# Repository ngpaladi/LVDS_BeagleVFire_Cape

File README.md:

# LVDS_BeagleVFire_Cape
Cape for LVDS inputs to a BeagleV Fire TDC

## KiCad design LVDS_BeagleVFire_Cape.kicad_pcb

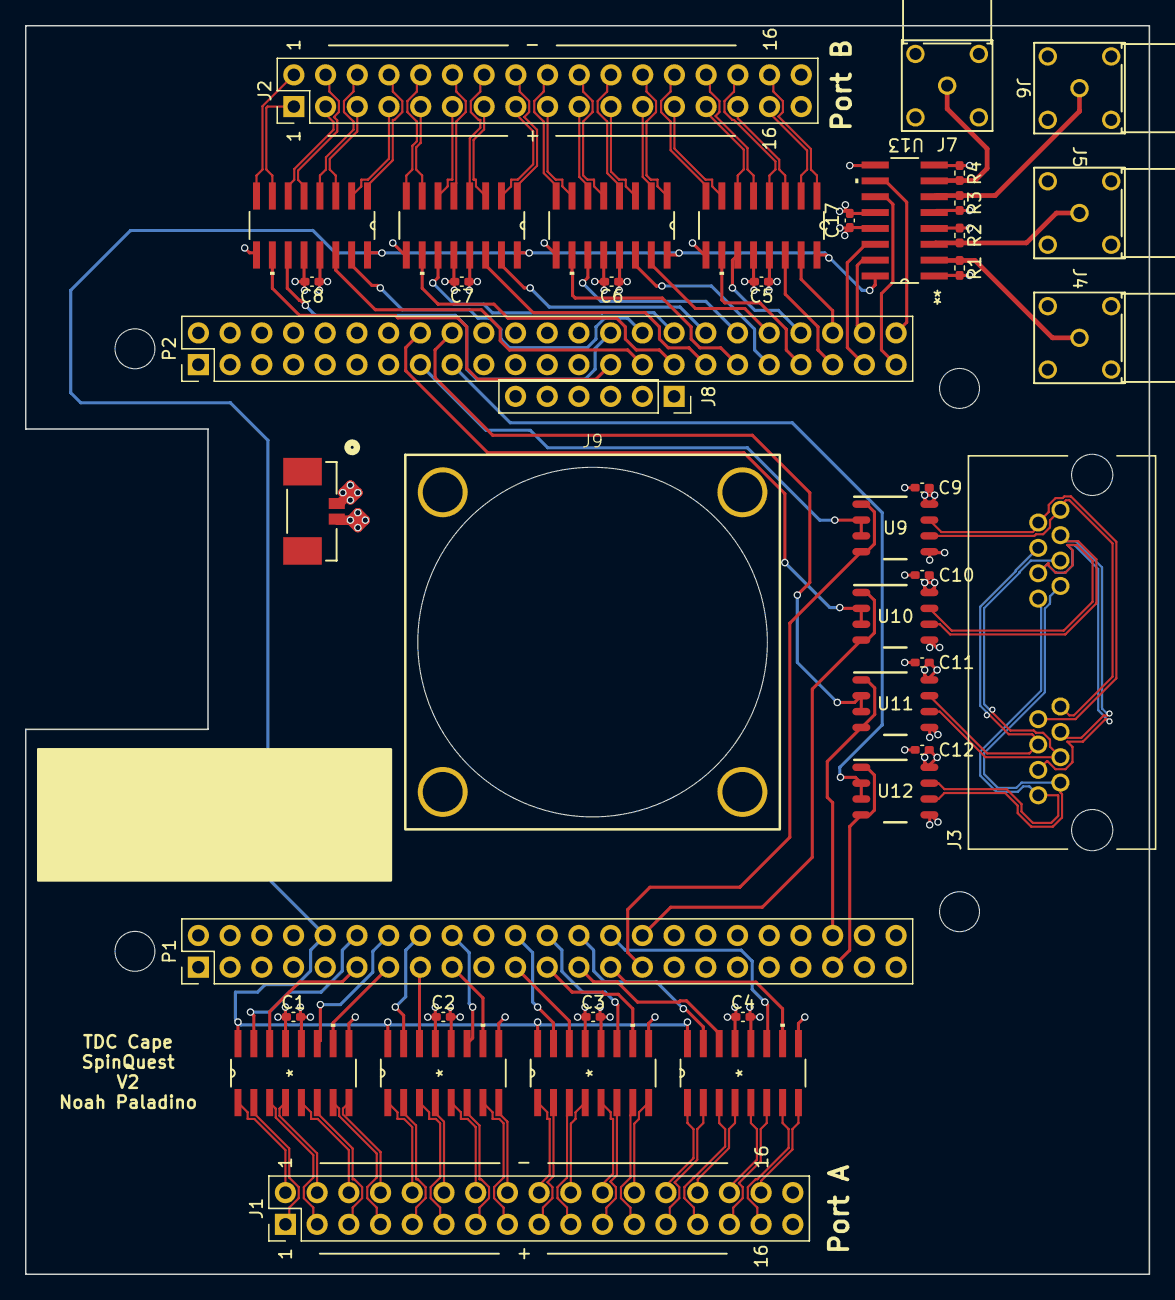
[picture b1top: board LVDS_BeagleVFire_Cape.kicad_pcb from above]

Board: 4 copper layers, 90.0 x 100.0 mm, 45 parts (0 on the bottom side), 125 nets.

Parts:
C1, C2, C3, C4, C5, C6, C7, C8, C9, C10, C11, C12, C17: C100n; C_0402_1005Metric_Pad0.74x0.62mm_HandSolder
J1, J2: Conn_02x16; PinHeader_2x17_P2.54mm_Vertical_ECL
J3: RJHSE508002; AMPHENOL_RJHSE508002
J4, J5, J6, J7: Conn_Coaxial_Small; CONN_EPK.00.250.NTN_LMO
J8: Conn_01x06_Pin; PinSocket_1x06_P2.54mm_Vertical
J9: LD3007MS_FAN
MH1, MH2, MH3, MH4: MountingHole_3.2mm_M3_DIN965
P1, P2: BeagleBone_Black_Header; PinHeader_2x23_P2.54mm_Vertical
R1, R2, R3, R4: R100; R_0402_1005Metric_Pad0.72x0.64mm_HandSolder
U1, U2, U3, U4, U5, U6, U7, U8, U13: SN65LVDT348D; D16
U9, U10, U11, U12: SN65MLVD206BD; D0008A_N

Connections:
+3V3: C1.1, C2.1, C3.1, C4.1, C5.1, C6.1, C7.1, C8.1, C9.1, C10.1, C11.1, C12.1, C17.1, P1.3, P1.4, U1.13 (VCC), U2.13 (VCC), U3.13 (VCC), U4.13 (VCC), U5.13 (VCC), U6.13 (VCC), U7.13 (VCC), U8.13 (VCC), U9.8 (VCC), U10.8 (VCC), U11.8 (VCC), U12.8 (VCC), U13.13 (VCC)
+5V: J9.2 (Fan+), P1.5, P1.6
/D0: P1.12, U1.15 (ROUT1)
/D1: P1.11, U1.14 (ROUT2)
/D2: P1.14, U1.11 (ROUT3)
/D3: P1.13, U1.10 (ROUT4)
/D4: P1.16, U2.15 (ROUT1)
/D5: P1.15, U2.14 (ROUT2)
/D6: P1.18, U2.11 (ROUT3)
/D7: P1.17, U2.10 (ROUT4)
/D8: P1.22, U3.15 (ROUT1)
/D9: P1.21, U3.14 (ROUT2)
/D10: P1.24, U3.11 (ROUT3)
/D11: P1.23, U3.10 (ROUT4)
/D12: P1.26, U4.15 (ROUT1)
/D13: P1.25, U4.14 (ROUT2)
/D14: P1.28, U4.11 (ROUT3)
/D15: P1.27, U4.10 (ROUT4)
/D16: P2.27, U8.10 (ROUT4)
/D17: P2.28, U8.11 (ROUT3)
/D18: P2.29, U8.14 (ROUT2)
/D19: P2.30, U8.15 (ROUT1)
/D20: P2.31, U7.10 (ROUT4)
/D21: P2.32, U7.11 (ROUT3)
/D22: P2.33, U7.14 (ROUT2)
/D23: P2.34, U7.15 (ROUT1)
/D24: P2.35, U6.10 (ROUT4)
/D25: P2.36, U6.11 (ROUT3)
/D26: P2.37, U6.14 (ROUT2)
/D27: P2.38, U6.15 (ROUT1)
/D28: P2.39, U5.10 (ROUT4)
/D29: P2.40, U5.11 (ROUT3)
/D30: P2.41, U5.14 (ROUT2)
/D31: P2.42, U5.15 (ROUT1)
/Discriminator Inputs/Port A/In0+: J1.1, U1.2 (RIN1+)
/Discriminator Inputs/Port A/In0-: J1.2, U1.1
/Discriminator Inputs/Port A/In1+: J1.3, U1.3 (RIN2+)
/Discriminator Inputs/Port A/In1-: J1.4, U1.4
/Discriminator Inputs/Port A/In2+: J1.5, U1.6 (RIN3+)
/Discriminator Inputs/Port A/In2-: J1.6, U1.5
/Discriminator Inputs/Port A/In3+: J1.7, U1.7 (RIN4+)
/Discriminator Inputs/Port A/In3-: J1.8, U1.8
/Discriminator Inputs/Port A/In4+: J1.9, U2.2 (RIN1+)
/Discriminator Inputs/Port A/In4-: J1.10, U2.1
/Discriminator Inputs/Port A/In5+: J1.11, U2.3 (RIN2+)
/Discriminator Inputs/Port A/In5-: J1.12, U2.4
/Discriminator Inputs/Port A/In6+: J1.13, U2.6 (RIN3+)
/Discriminator Inputs/Port A/In6-: J1.14, U2.5
/Discriminator Inputs/Port A/In7+: J1.15, U2.7 (RIN4+)
/Discriminator Inputs/Port A/In7-: J1.16, U2.8
/Discriminator Inputs/Port A/In8+: J1.17, U3.2 (RIN1+)
/Discriminator Inputs/Port A/In8-: J1.18, U3.1
/Discriminator Inputs/Port A/In9+: J1.19, U3.3 (RIN2+)
/Discriminator Inputs/Port A/In9-: J1.20, U3.4
/Discriminator Inputs/Port A/In10+: J1.21, U3.6 (RIN3+)
/Discriminator Inputs/Port A/In10-: J1.22, U3.5
/Discriminator Inputs/Port A/In11+: J1.23, U3.7 (RIN4+)
/Discriminator Inputs/Port A/In11-: J1.24, U3.8
/Discriminator Inputs/Port A/In12+: J1.25, U4.2 (RIN1+)
/Discriminator Inputs/Port A/In12-: J1.26, U4.1
/Discriminator Inputs/Port A/In13+: J1.27, U4.3 (RIN2+)
/Discriminator Inputs/Port A/In13-: J1.28, U4.4
/Discriminator Inputs/Port A/In14+: J1.29, U4.6 (RIN3+)
/Discriminator Inputs/Port A/In14-: J1.30, U4.5
/Discriminator Inputs/Port A/In15+: J1.31, U4.7 (RIN4+)
/Discriminator Inputs/Port A/In15-: J1.32, U4.8
/Discriminator Inputs/Port B/In0+: J2.31, U5.2 (RIN1+)
/Discriminator Inputs/Port B/In0-: J2.32, U5.1
/Discriminator Inputs/Port B/In1+: J2.29, U5.3 (RIN2+)
/Discriminator Inputs/Port B/In1-: J2.30, U5.4
/Discriminator Inputs/Port B/In2+: J2.27, U5.6 (RIN3+)
/Discriminator Inputs/Port B/In2-: J2.28, U5.5
/Discriminator Inputs/Port B/In3+: J2.25, U5.7 (RIN4+)
/Discriminator Inputs/Port B/In3-: J2.26, U5.8
/Discriminator Inputs/Port B/In4+: J2.23, U6.2 (RIN1+)
/Discriminator Inputs/Port B/In4-: J2.24, U6.1
/Discriminator Inputs/Port B/In5+: J2.21, U6.3 (RIN2+)
/Discriminator Inputs/Port B/In5-: J2.22, U6.4
/Discriminator Inputs/Port B/In6+: J2.19, U6.6 (RIN3+)
/Discriminator Inputs/Port B/In6-: J2.20, U6.5
/Discriminator Inputs/Port B/In7+: J2.17, U6.7 (RIN4+)
/Discriminator Inputs/Port B/In7-: J2.18, U6.8
/Discriminator Inputs/Port B/In8+: J2.15, U7.2 (RIN1+)
/Discriminator Inputs/Port B/In8-: J2.16, U7.1
/Discriminator Inputs/Port B/In9+: J2.13, U7.3 (RIN2+)
/Discriminator Inputs/Port B/In9-: J2.14, U7.4
/Discriminator Inputs/Port B/In10+: J2.11, U7.6 (RIN3+)
/Discriminator Inputs/Port B/In10-: J2.12, U7.5
/Discriminator Inputs/Port B/In11+: J2.9, U7.7 (RIN4+)
/Discriminator Inputs/Port B/In11-: J2.10, U7.8
/Discriminator Inputs/Port B/In12+: J2.7, U8.2 (RIN1+)
/Discriminator Inputs/Port B/In12-: J2.8, U8.1
/Discriminator Inputs/Port B/In13+: J2.5, U8.3 (RIN2+)
/Discriminator Inputs/Port B/In13-: J2.6, U8.4
/Discriminator Inputs/Port B/In14+: J2.3, U8.6 (RIN3+)
/Discriminator Inputs/Port B/In14-: J2.4, U8.5
/Discriminator Inputs/Port B/In15+: J2.1, U8.7 (RIN4+)
/Discriminator Inputs/Port B/In15-: J2.2, U8.8
/NIM0: P2.44, U13.15 (ROUT1)
/NIM1: P2.43, U13.14 (ROUT2)
/NIM2: P2.45, U13.11 (ROUT3)
/NIM3: P2.46, U13.10 (ROUT4)
/TS_BUS0: P1.29, U9.1 (R), U9.4 (D)
/TS_BUS1: P1.30, U10.1 (R), U10.4 (D)
/TS_BUS2: P1.42, U11.1 (R), U11.4 (D)
/TS_BUS3: P1.41, U12.1 (R), U12.4 (D)
/TS_BUS_SEL0: P2.15, U9.2 (RE_N), U9.3 (DE)
/TS_BUS_SEL1: P2.16, U10.2 (RE_N), U10.3 (DE)
/TS_BUS_SEL2: P2.18, U11.2 (RE_N), U11.3 (DE)
/TS_BUS_SEL3: P2.17, U12.2 (RE_N), U12.3 (DE)
/Trigger Interface/D1+: J3.1_1, J3.2_1, U9.6 (A)
/Trigger Interface/D1-: J3.1_2, J3.2_2, U9.7 (B)
/Trigger Interface/D2+: J3.1_3, J3.2_3, U10.6 (A)
/Trigger Interface/D2-: J3.1_6, J3.2_6, U10.7 (B)
/Trigger Interface/D3+: J3.1_5, J3.2_5, U11.6 (A)
/Trigger Interface/D3-: J3.1_4, J3.2_4, U11.7 (B)
/Trigger Interface/D4+: J3.1_7, J3.2_7, U12.6 (A)
/Trigger Interface/D4-: J3.1_8, J3.2_8, U12.7 (B)
/Trigger Interface/NIM1+: J4.1 (In), R1.2, U13.2 (RIN1+)
/Trigger Interface/NIM2+: J5.1 (In), R2.2, U13.3 (RIN2+)
/Trigger Interface/NIM3+: J6.1 (In), R3.1, U13.6 (RIN3+)
/Trigger Interface/NIM4+: J7.1 (In), R4.1, U13.7 (RIN4+)
GND: C1.2, C2.2, C3.2, C4.2, C5.2, C6.2, C7.2, C8.2, C9.2, C10.2, C11.2, C12.2, C17.2, J4.2 (Ext), J5.2 (Ext), J6.2 (Ext), J7.2 (Ext), J9.1 (Fan-), P1.1, P1.2, P1.43, P1.44, P1.45, P1.46, P2.1, P2.2, R1.1, R2.1, R3.2, R4.2, U1.9 (*EN), U1.12 (GND), U2.9 (*EN), U2.12 (GND), U3.9 (*EN), U3.12 (GND), U4.9 (*EN), U4.12 (GND), U5.9 (*EN), U5.12 (GND), U6.9 (*EN), U6.12 (GND), U7.9 (*EN), U7.12 (GND), U8.9 (*EN), U8.12 (GND), U9.5 (GND), U10.5 (GND), U11.5 (GND), U12.5 (GND), U13.1, U13.4, U13.5, U13.8, U13.9 (*EN), U13.12 (GND)
VBUS: P1.7, P1.8
~SYS_RESET: P1.10, U1.16 (EN), U2.16 (EN), U3.16 (EN), U4.16 (EN), U5.16 (EN), U6.16 (EN), U7.16 (EN), U8.16 (EN), U13.16 (EN)

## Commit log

2024-10-02 Hardware v1
2025-03-19 Add Stencil Layers
